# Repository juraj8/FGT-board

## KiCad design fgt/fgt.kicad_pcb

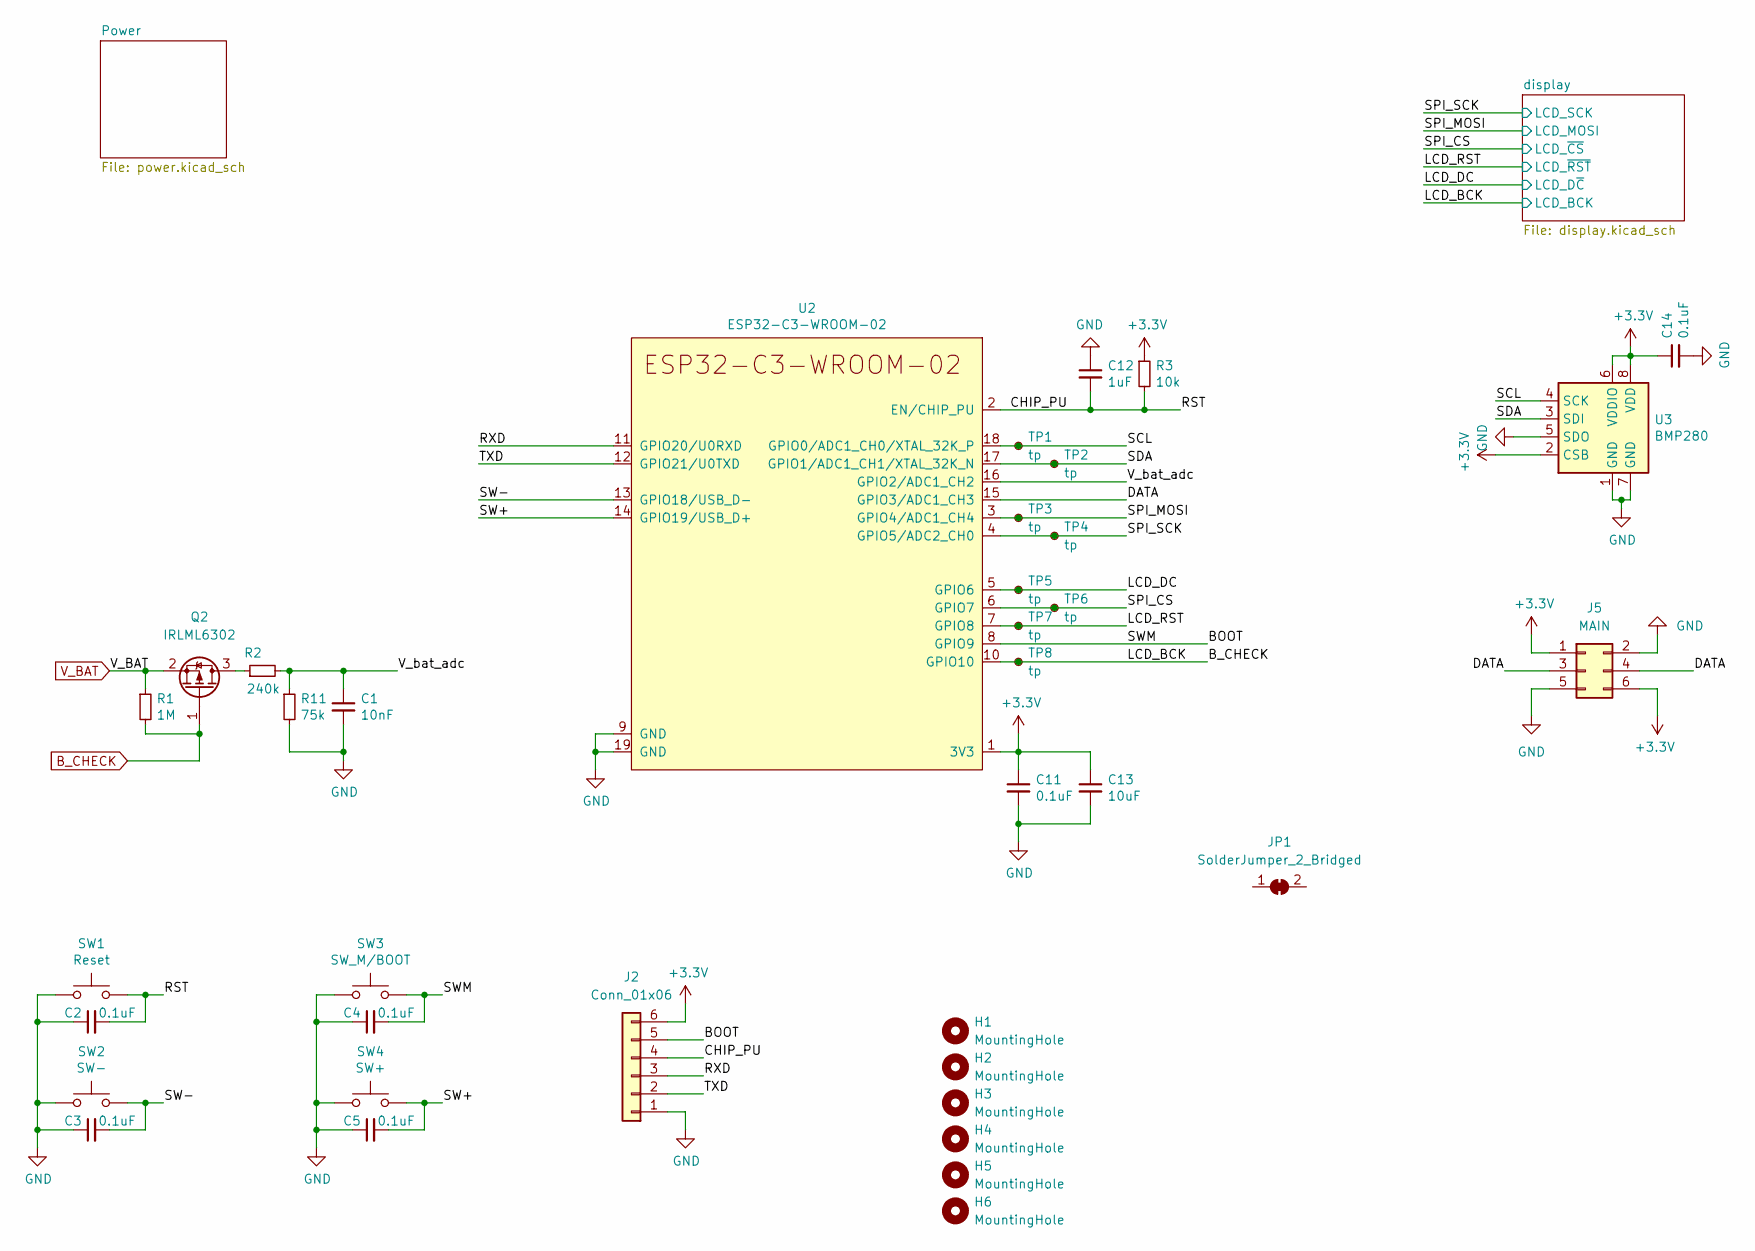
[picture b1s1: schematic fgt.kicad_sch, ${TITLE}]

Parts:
C1: 10nF; C_0805_2012Metric
C2, C3, C4, C5: 0.1uF; C_0805_2012Metric
C11, C14: 0.1uF; C_0603_1608Metric
C12: 1uF; C_0603_1608Metric
C13: 10uF; C_0805_2012Metric
H1, H2, H3, H4, H5, H6: MountingHole; MountingHole_3.2mm_M3_DIN965
J2: Conn_01x06; PinHeader_1x06_P2.54mm_Vertical
J5: MAIN; IDC-Header_2x03_P2.54mm_Vertical
JP1: SolderJumper_2_Bridged; SolderJumper-2_P1.3mm_Bridged_RoundedPad1.0x1.5mm
Q2: IRLML6302; SOT-23
R1: 1M; R_0805_2012Metric
R2: 240k; R_0805_2012Metric
R3: 10k; R_0805_2012Metric
R11: 75k; R_0805_2012Metric
SW1: Reset; SW_SPST_SKQG_WithStem
SW2: SW-; SW_SPST_SKQG_WithStem
SW3: SW_M/BOOT; SW_SPST_SKQG_WithStem
SW4: SW+; SW_SPST_SKQG_WithStem
TP1, TP2, TP3, TP4, TP5, TP6, TP7, TP8: tp; TestPoint_Pad_D1.0mm
U2: ESP32-C3-WROOM-02
U3: BMP280; Bosch_LGA-8_2x2.5mm_P0.65mm_ClockwisePinNumbering

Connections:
+3V3: C11.1, C13.1, C14.1, J2.6, J5.1, J5.6, R3.1, U2.1 (3V3), U3.2 (CSB), U3.6 (VDDIO), U3.8 (VDD); also elsewhere on the board
/CHIP_PU: C2.2, C12.2, J2.4, R3.2, SW1.2, U2.2 (EN/CHIP_PU)
/DATA: J5.3, J5.4, U2.15 (GPIO3/ADC1_CH3)
/LCD_DC: TP5.1, U2.5 (GPIO6); also elsewhere on the board
/LCD_RST: TP7.1, U2.7 (GPIO8); also elsewhere on the board
/RXD: J2.3, U2.11 (GPIO20/U0RXD)
/SCL: TP1.1, U2.18 (GPIO0/ADC1_CH0/XTAL_32K_P), U3.4 (SCK)
/SDA: TP2.1, U2.17 (GPIO1/ADC1_CH1/XTAL_32K_N), U3.3 (SDI)
/SPI_CS: TP6.1, U2.6 (GPIO7); also elsewhere on the board
/SPI_MOSI: TP3.1, U2.3 (GPIO4/ADC1_CH4); also elsewhere on the board
/SPI_SCK: TP4.1, U2.4 (GPIO5/ADC2_CH0); also elsewhere on the board
/SW+: C5.2, SW4.2, U2.14 (GPIO19/USB_D+)
/SW-: C3.2, SW2.2, U2.13 (GPIO18/USB_D-)
/SWM: C4.2, J2.5, SW3.2, U2.8 (GPIO9)
/TXD: J2.2, U2.12 (GPIO21/U0TXD)
/V_bat_adc: C1.1, R2.2, R11.1, U2.16 (GPIO2/ADC1_CH2)
B_CHECK: Q2.1 (G), R1.2, TP8.1, U2.10 (GPIO10); also elsewhere on the board
GND: C1.2, C2.1, C3.1, C4.1, C5.1, C11.2, C12.1, C13.2, C14.2, J2.1, J5.2, J5.5, R11.2, SW1.1, SW2.1, SW3.1, SW4.1, U2.9 (GND), U2.19 (GND), U3.1 (GND), U3.5 (SDO), U3.7 (GND); also elsewhere on the board
unnamed: Q2.3 (D), R2.1
V_BAT: Q2.2 (S), R1.1; also elsewhere on the board

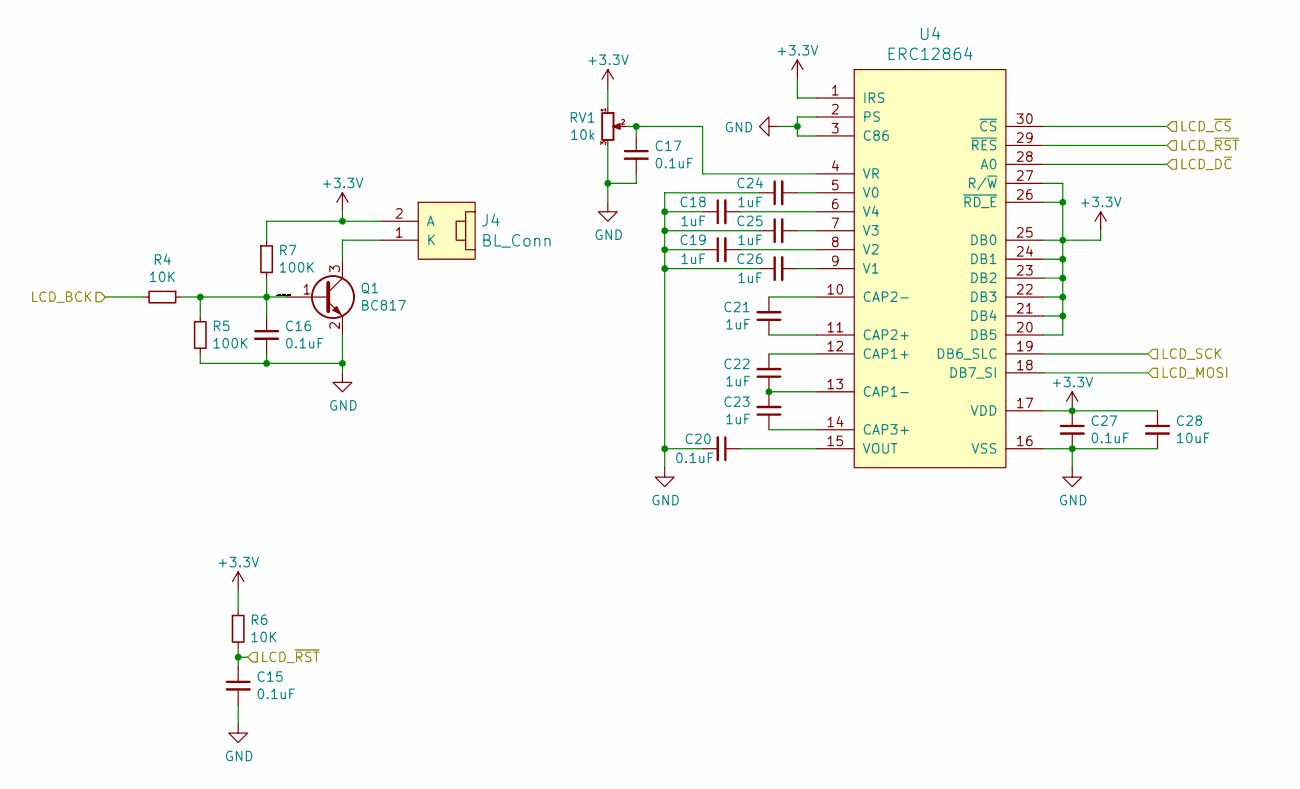
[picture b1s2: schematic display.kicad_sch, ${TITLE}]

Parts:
C15, C16, C17, C20, C27: 0.1uF; C_0603_1608Metric
C18, C19, C21, C22, C23, C24, C25, C26: 1uF; C_0603_1608Metric
C28: 10uF; C_0805_2012Metric
J4: BL_Conn; ER-CON2.0-2P-SMD
Q1: BC817; SOT-23
R4, R6: 10K; R_0805_2012Metric
R5, R7: 100K; R_0805_2012Metric
RV1: 10k; Potentiometer_Vishay_TS53YJ_Vertical
U4: ERC12864; ER-CON30HB-1

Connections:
+3V3: C27.1, C28.1, J4.2 (A), R6.1, R7.1, RV1.1, U4.1 (IRS), U4.17 (VDD), U4.20 (DB5), U4.21 (DB4), U4.22 (DB3), U4.23 (DB2), U4.24 (DB1), U4.25 (DB0), U4.26 (~RD_E), U4.27 (R/~W); also elsewhere on the board
/LCD_DC: U4.28 (A0); also elsewhere on the board
/LCD_RST: C15.1, R6.2, U4.29 (~RES); also elsewhere on the board
/SPI_CS: U4.30 (~CS); also elsewhere on the board
/SPI_MOSI: U4.18 (DB7_SI); also elsewhere on the board
/SPI_SCK: U4.19 (DB6_SLC); also elsewhere on the board
/display/_lcd_bck_cnt: C16.1, Q1.1 (B), R4.1, R5.1, R7.2
B_CHECK: R4.2; also elsewhere on the board
GND: C15.2, C16.2, C17.2, C18.1, C19.1, C20.2, C24.1, C25.1, C26.1, C27.2, C28.2, Q1.2 (E), R5.2, RV1.3, U4.2 (PS), U4.3 (C86), U4.16 (VSS); also elsewhere on the board
unnamed: C17.1, RV1.2, U4.4 (VR)
unnamed: C18.2, U4.6 (V4)
unnamed: C19.2, U4.8 (V2)
unnamed: C20.1, U4.15 (VOUT)
unnamed: C21.1, U4.11 (CAP2+)
unnamed: C21.2, U4.10 (CAP2-)
unnamed: C22.1, C23.2, U4.13 (CAP1-)
unnamed: C22.2, U4.12 (CAP1+)
unnamed: C23.1, U4.14 (CAP3+)
unnamed: C24.2, U4.5 (V0)
unnamed: C25.2, U4.7 (V3)
unnamed: C26.2, U4.9 (V1)
unnamed: J4.1 (K), Q1.3 (C)

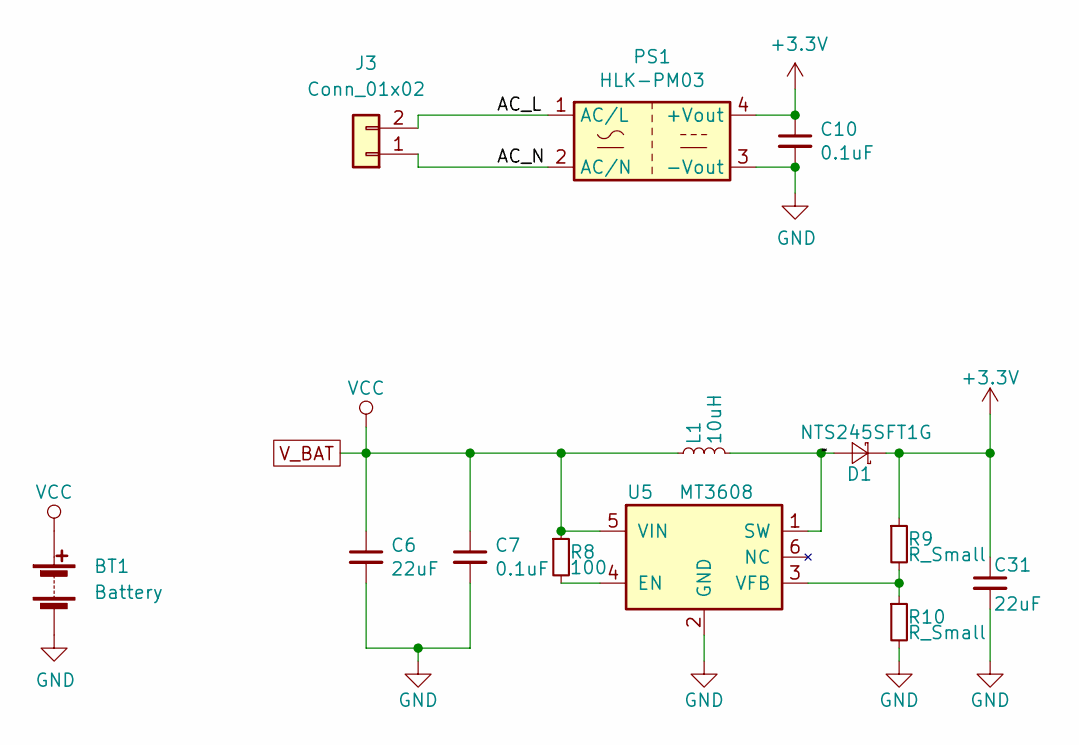
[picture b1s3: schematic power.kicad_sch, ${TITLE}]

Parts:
BT1: Battery; ER-CON2.0-2P-SMD
C6, C31: 22uF; C_0805_2012Metric
C7, C10: 0.1uF; C_0805_2012Metric
D1: NTS245SFT1G; D_SOD-123
J3: Conn_01x02; PhoenixContact_MSTBVA_2,5_2-G-5,08_1x02_P5.08mm_Vertical
L1: 10uH; L_1008_2520Metric
PS1: HLK-PM03; Converter_ACDC_HiLink_HLK-PMxx
R8: 100; R_0805_2012Metric
R9, R10: R_Small; R_0805_2012Metric
U5: MT3608; SOT-23-6

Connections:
+3V3: C10.1, C31.1, D1.1 (K), PS1.4 (+Vout), R9.1; also elsewhere on the board
/Power/AC_L: J3.2, PS1.1 (AC/L)
/Power/AC_N: J3.1, PS1.2 (AC/N)
/Power/sw: D1.2 (A), L1.2, U5.1 (SW)
GND: BT1.2 (-), C6.2, C7.2, C10.2, C31.2, PS1.3 (-Vout), R10.2, U5.2 (GND); also elsewhere on the board
unnamed: R9.2, R10.1, U5.3 (VFB)
unnamed: R8.2, U5.4 (EN)
V_BAT: BT1.1 (+), C6.1, C7.1, L1.1, R8.1, U5.5 (VIN); also elsewhere on the board

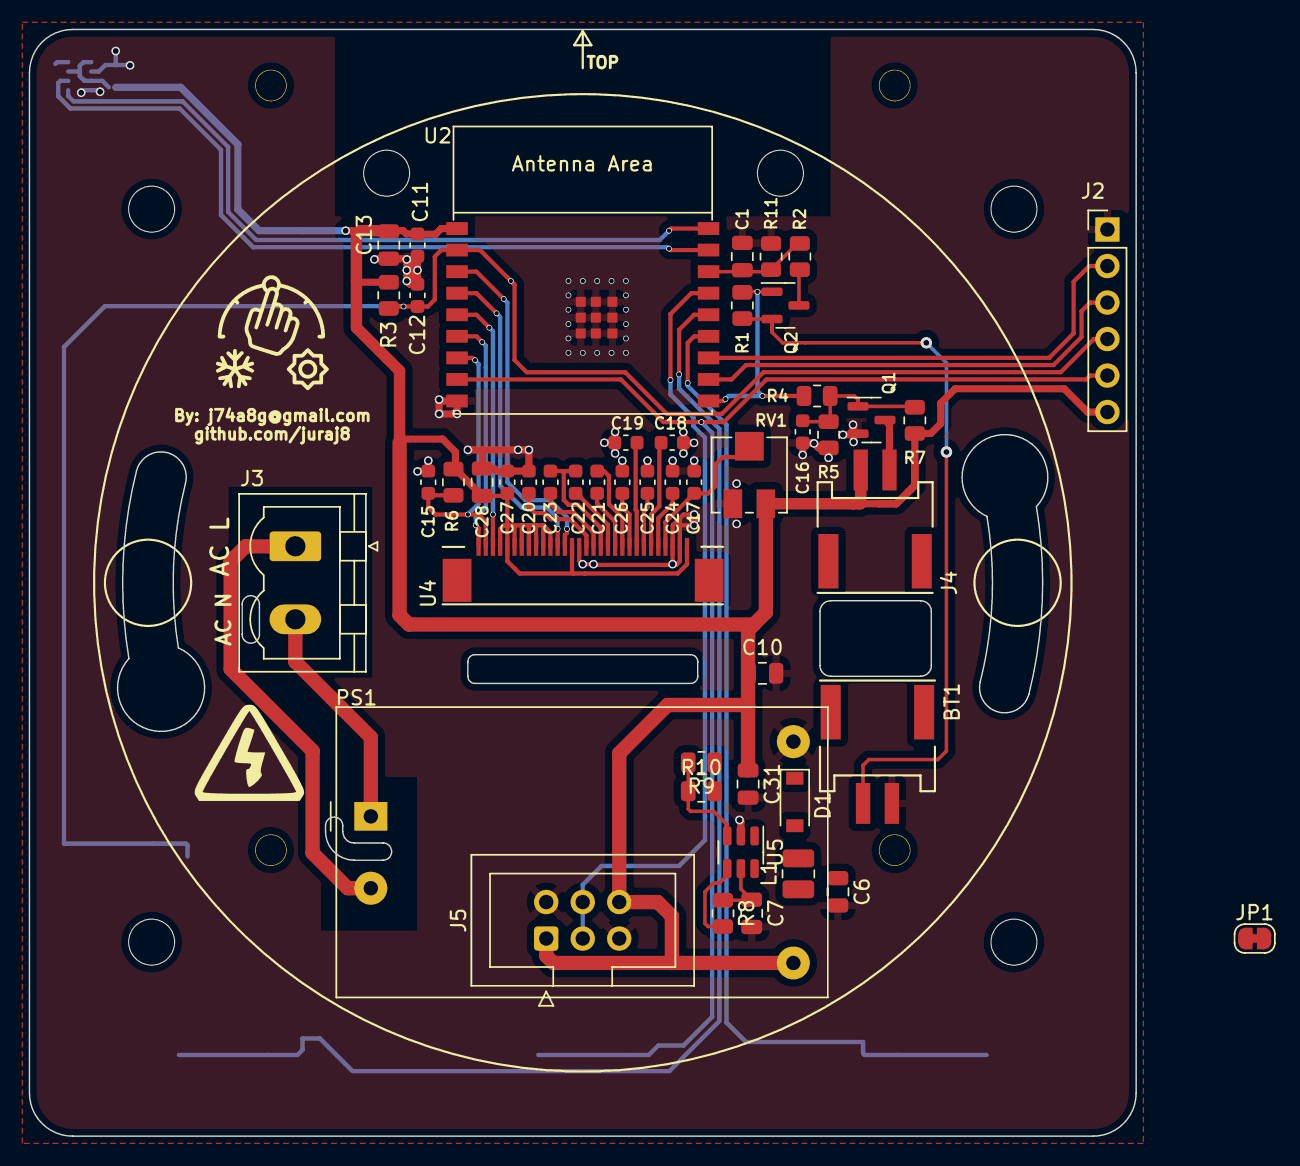
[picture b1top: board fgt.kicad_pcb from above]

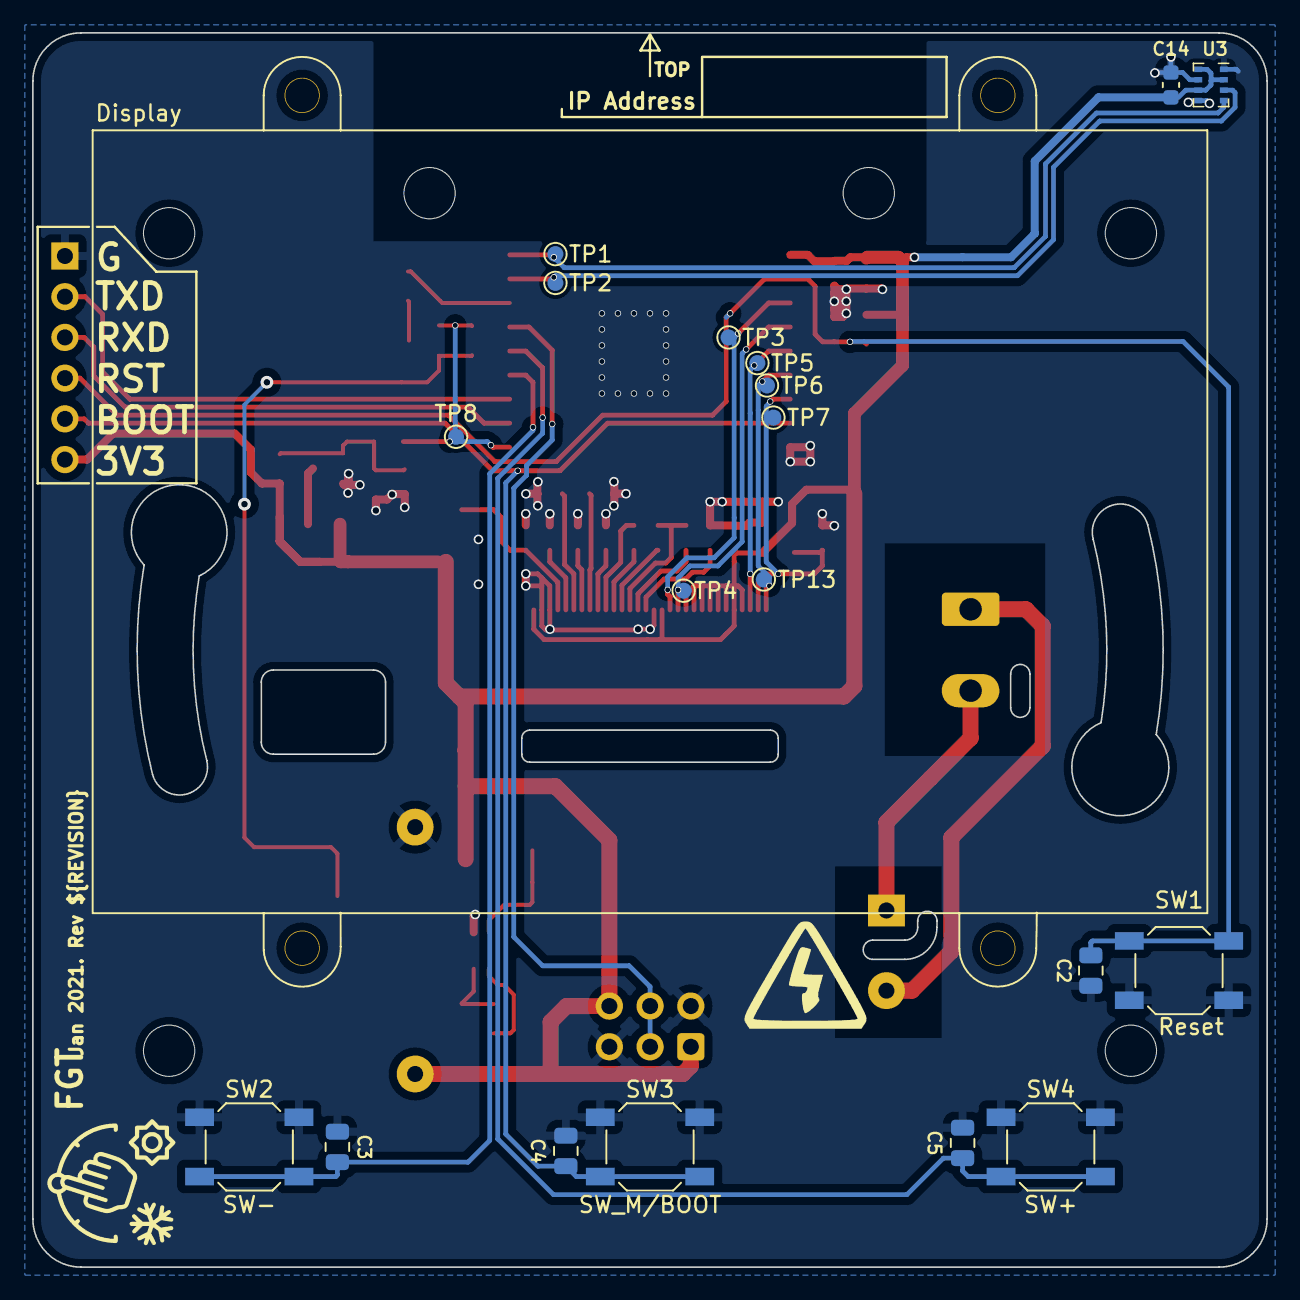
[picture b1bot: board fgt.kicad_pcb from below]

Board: 2 copper layers, 77.0 x 77.0 mm, 74 parts (20 on the bottom side), 39 nets.

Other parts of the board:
Display: ER-DISP
TP13: tp; TestPoint_Pad_D1.0mm

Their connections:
/SPI_CS: TP13.1; also elsewhere on the board

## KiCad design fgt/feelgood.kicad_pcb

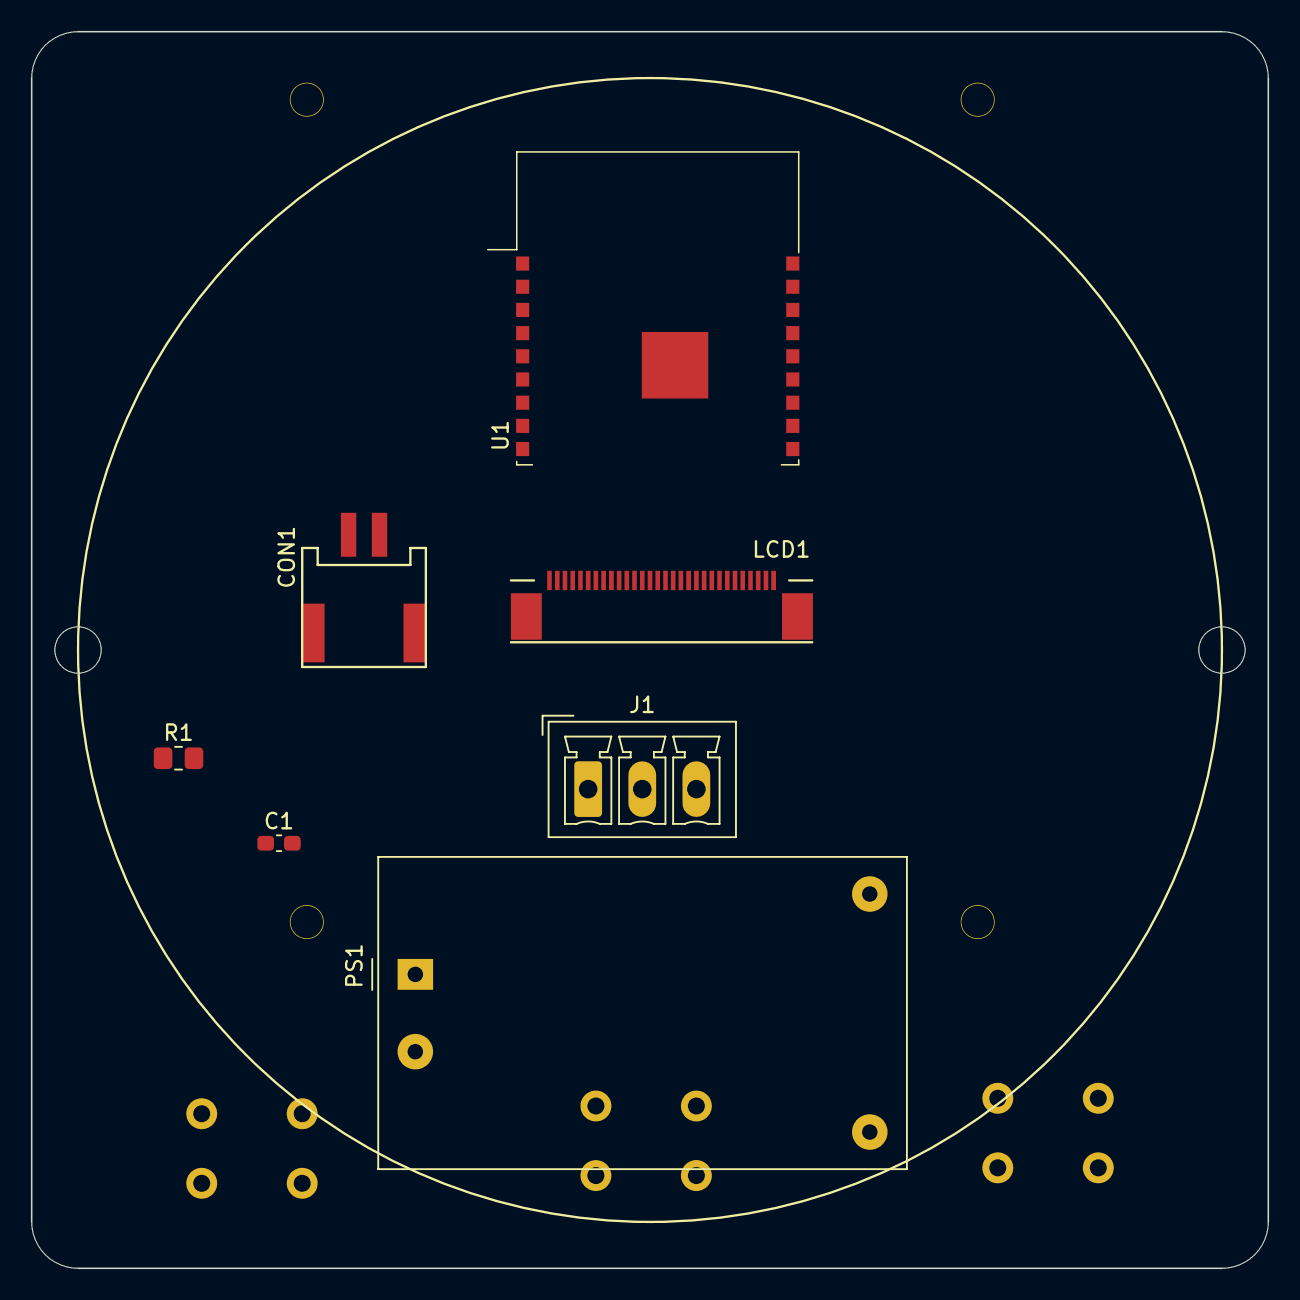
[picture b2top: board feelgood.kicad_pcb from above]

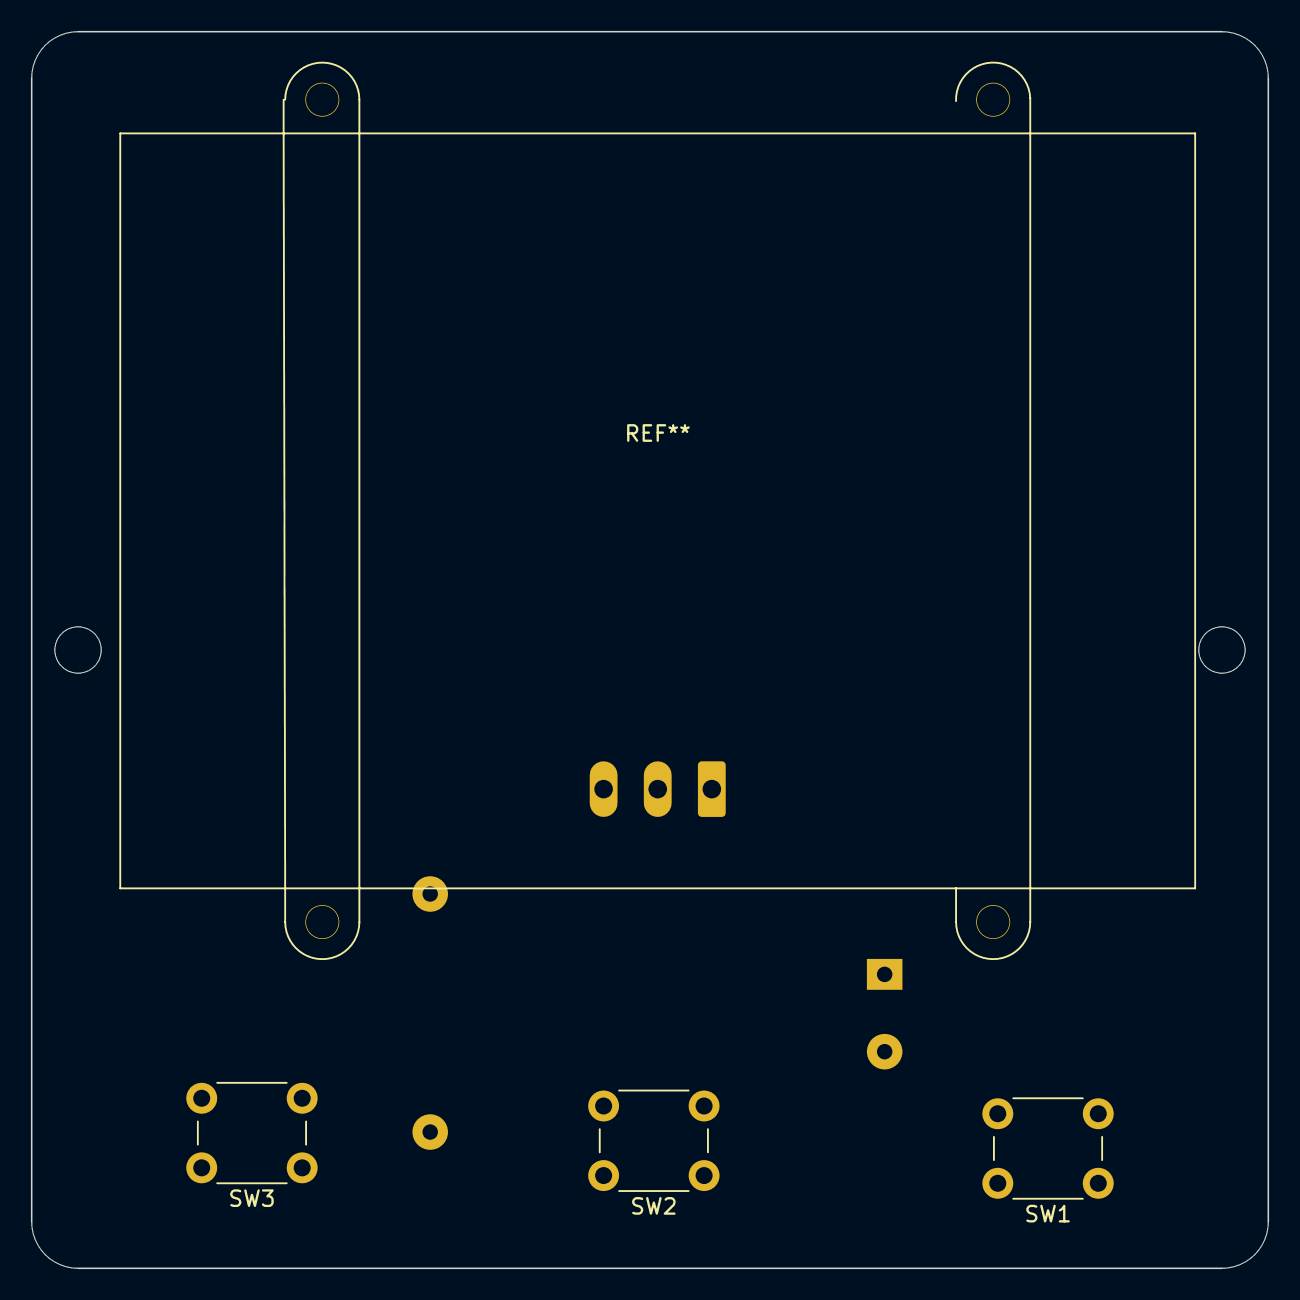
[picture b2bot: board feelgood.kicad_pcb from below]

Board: 2 copper layers, 80.0 x 80.0 mm, 10 parts (3 on the bottom side), 5 nets, no tracks yet.

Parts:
C1: 0.1uF; C_0603_1608Metric_Pad1.08x0.95mm_HandSolder
CON1: BL_CON; ER-CON2.0-2P-SMD
J1: Conn_01x03; PhoenixContact_MCV_1,5_3-G-3.5_1x03_P3.50mm_Vertical
LCD1: ERC12864; ER-CON30HB-1
PS1: HLK-PM03; Converter_ACDC_HiLink_HLK-PMxx
R1: 10k; R_0805_2012Metric_Pad1.20x1.40mm_HandSolder
SW1, SW2, SW3: SW_Push; SW_PUSH_6mm
U1: ESP-WROOM-02

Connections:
+3V3: C1.1, PS1.4
GND: C1.2, PS1.3
unnamed: J1.1, PS1.2
unnamed: J1.3, PS1.1
unnamed: U1.9, U1.13, U1.18, U1.19

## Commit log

2021-12-28 Almost finished layout
2022-01-01 placing locating holes
2022-01-02 layout done v1.0.0
2022-01-04 retouch board layout v1.1.0
2022-01-04 DRC done
2022-01-24 Release v1.4.0 - added testpoints - fix solder mask - size down pcb
2022-07-24 Release v1.5.0 - See changelog for changes.
